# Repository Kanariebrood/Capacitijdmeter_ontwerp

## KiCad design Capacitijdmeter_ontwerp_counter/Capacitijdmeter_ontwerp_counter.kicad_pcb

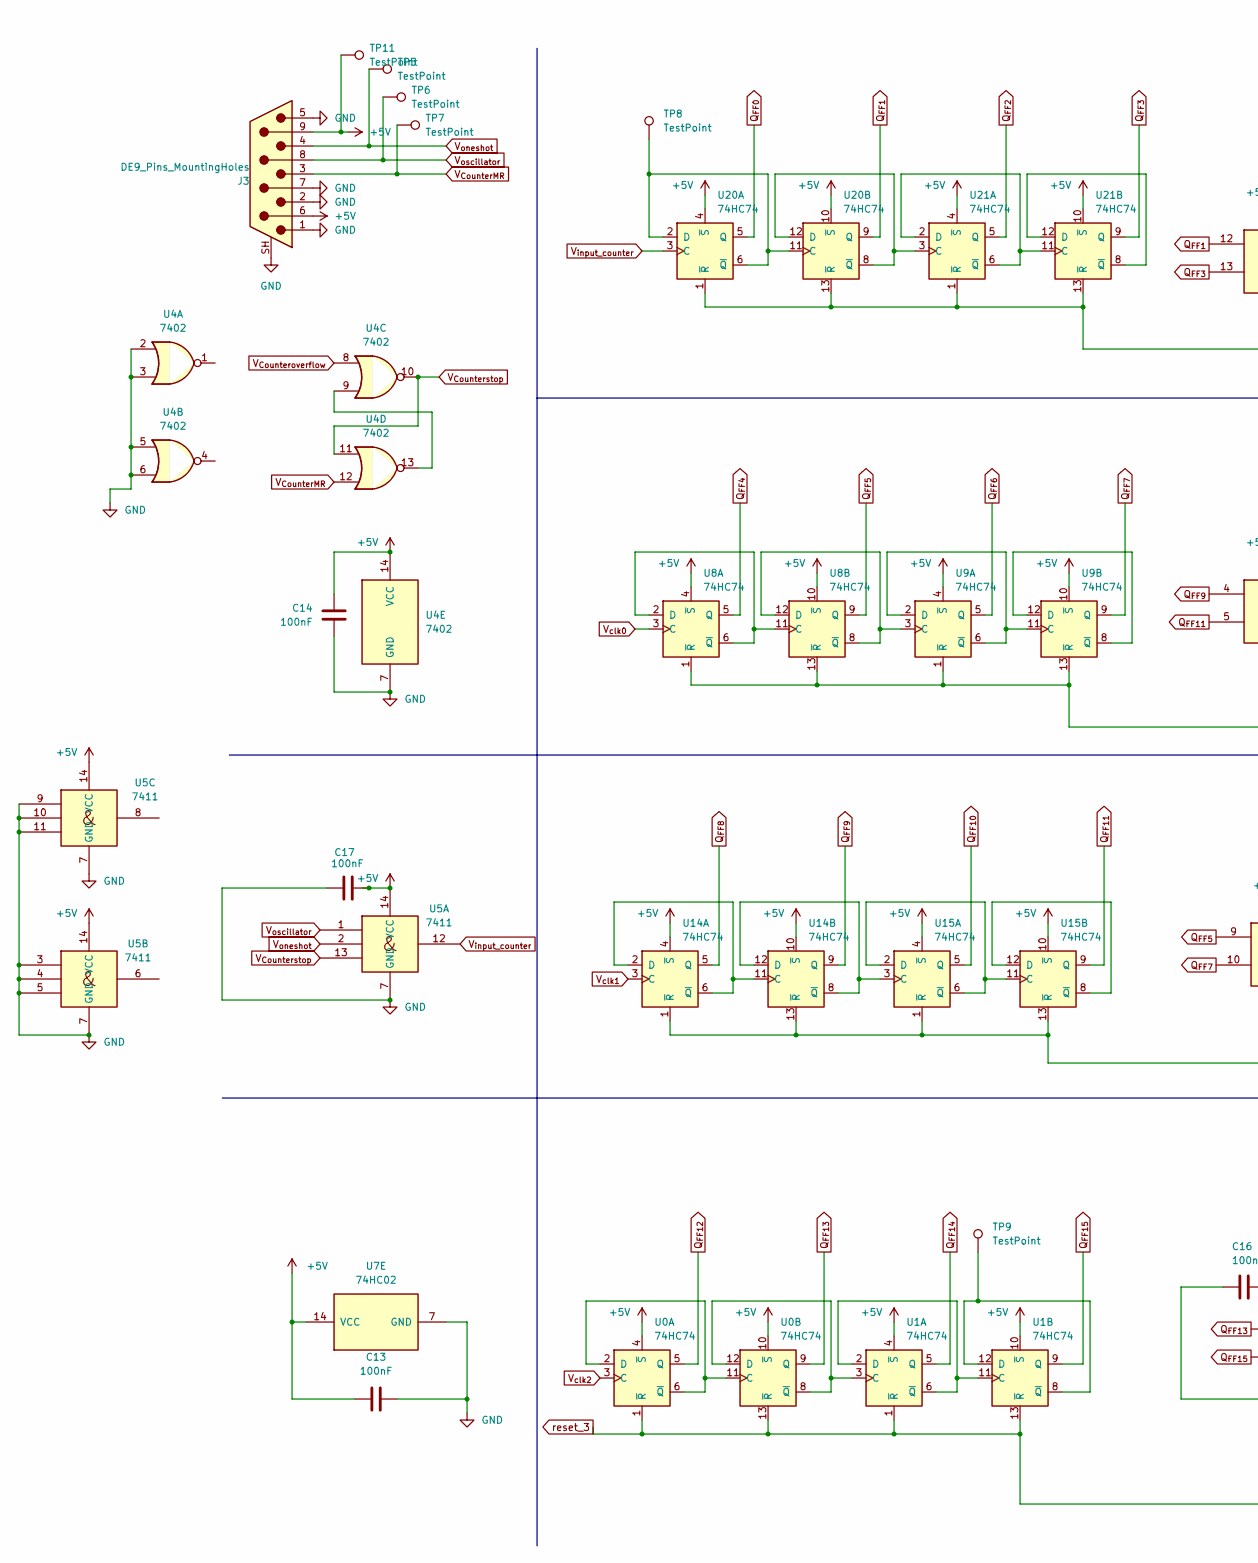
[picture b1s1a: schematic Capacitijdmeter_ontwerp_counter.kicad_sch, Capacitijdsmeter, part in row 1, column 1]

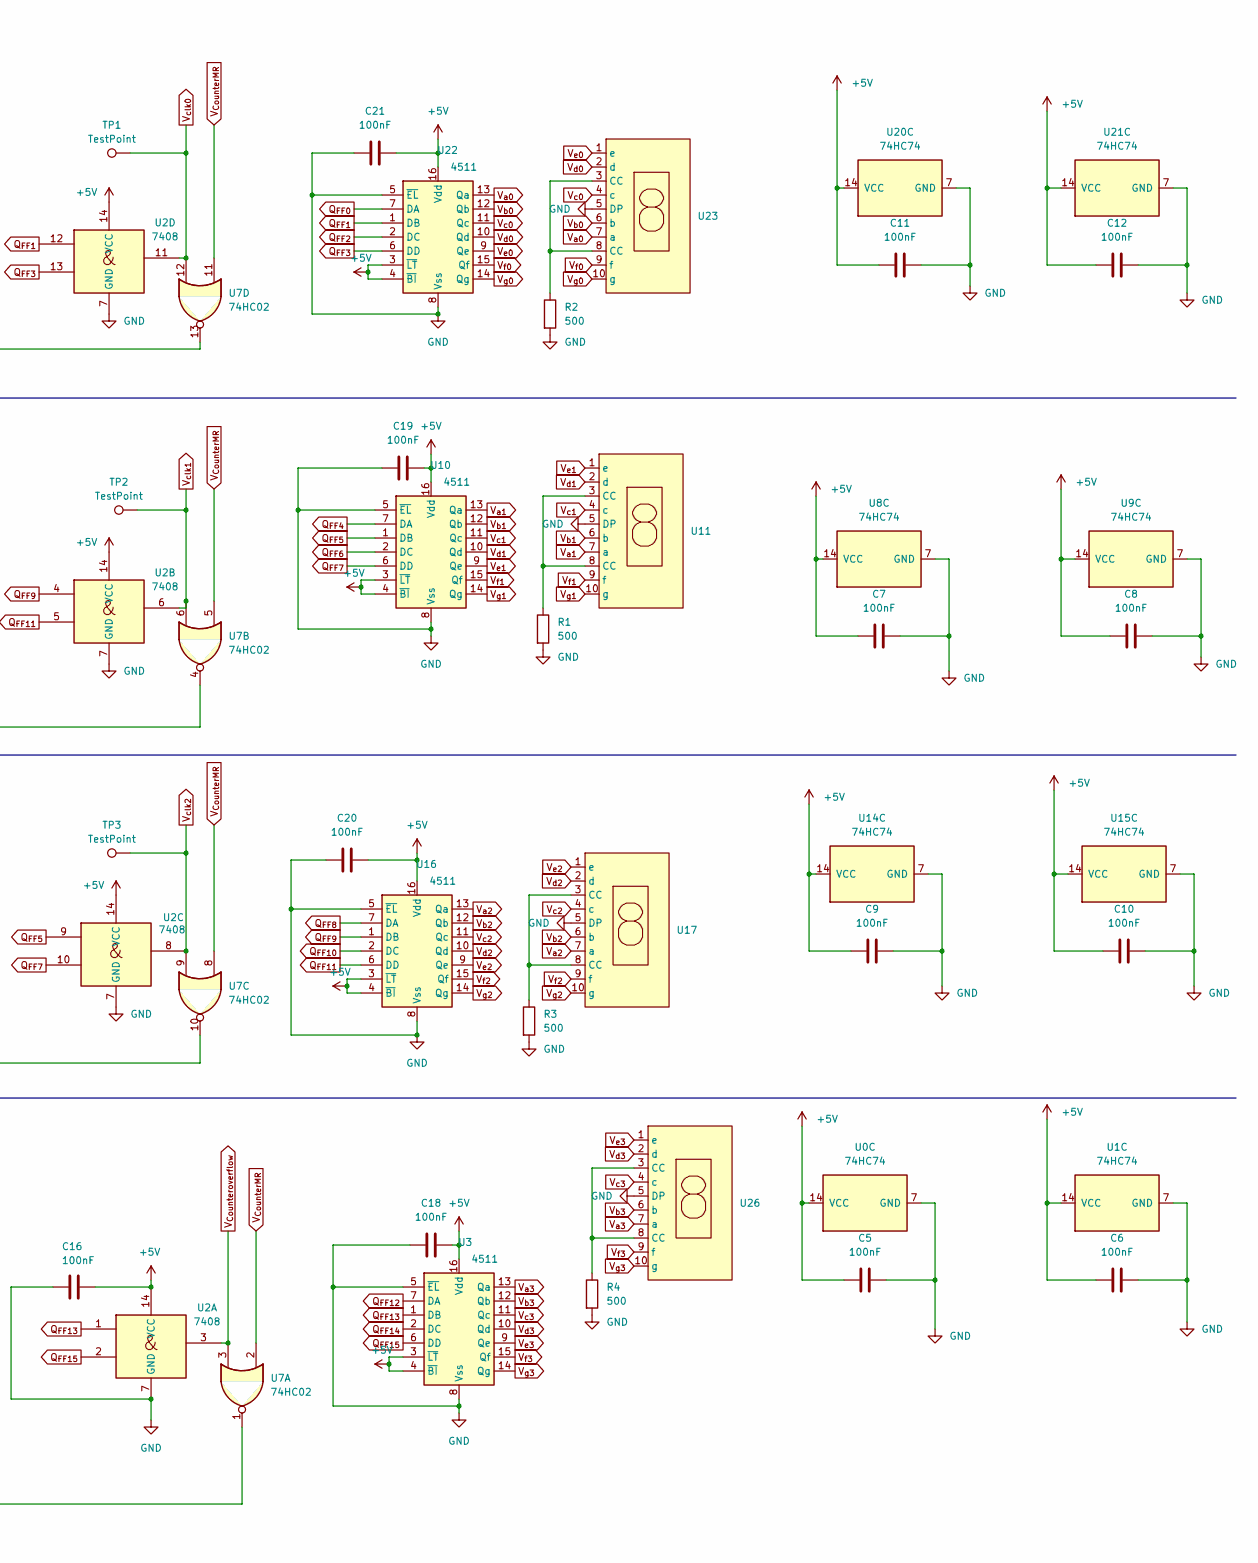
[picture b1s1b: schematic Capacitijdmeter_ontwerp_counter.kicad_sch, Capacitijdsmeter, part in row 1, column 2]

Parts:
C5, C6, C7, C8, C9, C10, C11, C12, C13, C14, C16, C17, C18, C19, C20, C21: 100nF; C_1206_3216Metric_Pad1.33x1.80mm_HandSolder
J3: DE9_Pins_MountingHoles; DSUB-9_Pins_Horizontal_P2.77x2.84mm_EdgePinOffset7.70mm_Hou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
R1, R2, R3, R4: 500; R_1206_3216Metric_Pad1.30x1.75mm_HandSolder
TP1, TP2, TP3, TP5, TP6, TP7, TP8, TP9, TP11: TestPoint; PinHeader_1x01_P1.00mm_Vertical
U0, U1, U8, U9, U14, U15, U20, U21: 74HC74; SOIC-14_3.9x8.7mm_P1.27mm
U2: 7408; SOIC-14_3.9x8.7mm_P1.27mm
U3, U10, U16, U22: 4511; JEITA_SOIC-16_3.9x9.9mm_P1.27mm
U4: 7402; SOIC-14_3.9x8.7mm_P1.27mm
U5: 7411; SOIC-14_3.9x8.7mm_P1.27mm
U7: 74HC02; SOIC-14_3.9x8.7mm_P1.27mm
U11, U17, U23, U26: SC56-11EWA_KNB

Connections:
+5V: C5.1, C6.1, C7.1, C8.1, C9.1, C10.1, C11.1, C12.1, C13.1, C14.2, C16.2, C17.2, C18.1, C19.1, C20.1, C21.1, J3.6, J3.9, TP11.1 (1_1), U0.4 (~S), U0.10 (~S), U0.14 (VCC), U1.4 (~S), U1.10 (~S), U1.14 (VCC), U2.14 (VCC), U3.3 (~LT), U3.4 (~BI), U3.16 (Vdd), U4.14 (VCC), U5.14 (VCC), U7.14 (VCC), U8.4 (~S), U8.10 (~S), U8.14 (VCC), U9.4 (~S), U9.10 (~S), U9.14 (VCC), U10.3 (~LT), U10.4 (~BI), U10.16 (Vdd), U14.4 (~S), U14.10 (~S), U14.14 (VCC), U15.4 (~S), U15.10 (~S), U15.14 (VCC), U16.3 (~LT), U16.4 (~BI), U16.16 (Vdd), U20.4 (~S), U20.10 (~S), U20.14 (VCC), U21.4 (~S), U21.10 (~S), U21.14 (VCC), U22.3 (~LT), U22.4 (~BI), U22.16 (Vdd)
GND: C5.2, C6.2, C7.2, C8.2, C9.2, C10.2, C11.2, C12.2, C13.2, C14.1, C16.1, C17.1, C18.2, C19.2, C20.2, C21.2, J3.1, J3.2, J3.5, J3.7, J3.SH (PAD), R1.2, R2.2, R3.2, R4.2, U0.7 (GND), U1.7 (GND), U2.7 (GND), U3.5 (~EL), U3.8 (Vss), U4.2, U4.3, U4.5, U4.6, U4.7 (GND), U5.3, U5.4, U5.5, U5.7 (GND), U5.9, U5.10, U5.11, U7.7 (GND), U8.7 (GND), U9.7 (GND), U10.5 (~EL), U10.8 (Vss), U11.5 (DP), U14.7 (GND), U15.7 (GND), U16.5 (~EL), U16.8 (Vss), U17.5 (DP), U20.7 (GND), U21.7 (GND), U22.5 (~EL), U22.8 (Vss), U23.5 (DP), U26.5 (DP)
unnamed: R1.1, U11.3 (CC), U11.8 (CC)
unnamed: R2.1, U23.3 (CC), U23.8 (CC)
unnamed: R3.1, U17.3 (CC), U17.8 (CC)
unnamed: R4.1, U26.3 (CC), U26.8 (CC)
unnamed: U0.2 (D), U0.6 (~Q), U0.11 (C)
unnamed: U0.8 (~Q), U0.12 (D), U1.3 (C)
unnamed: U1.2 (D), U1.6 (~Q), U1.11 (C)
unnamed: TP9.1 (1_1), U1.8 (~Q), U1.12 (D)
unnamed: U4.9, U4.13
unnamed: U8.2 (D), U8.6 (~Q), U8.11 (C)
unnamed: U7.4, U8.1 (~R), U8.13 (~R), U9.1 (~R), U9.13 (~R)
unnamed: U8.8 (~Q), U8.12 (D), U9.3 (C)
unnamed: U9.2 (D), U9.6 (~Q), U9.11 (C)
unnamed: U9.8 (~Q), U9.12 (D)
unnamed: U14.2 (D), U14.6 (~Q), U14.11 (C)
unnamed: U7.10, U14.1 (~R), U14.13 (~R), U15.1 (~R), U15.13 (~R)
unnamed: U14.8 (~Q), U14.12 (D), U15.3 (C)
unnamed: U15.2 (D), U15.6 (~Q), U15.11 (C)
unnamed: U15.8 (~Q), U15.12 (D)
unnamed: TP8.1 (1_1), U20.2 (D), U20.6 (~Q), U20.11 (C)
unnamed: U7.13, U20.1 (~R), U20.13 (~R), U21.1 (~R), U21.13 (~R)
unnamed: U20.8 (~Q), U20.12 (D), U21.3 (C)
unnamed: U21.2 (D), U21.6 (~Q), U21.11 (C)
unnamed: U21.8 (~Q), U21.12 (D)
Q_{FF0}: U20.5 (Q), U22.7 (DA)
Q_{FF1}: U2.12, U20.9 (Q), U22.1 (DB)
Q_{FF2}: U21.5 (Q), U22.2 (DC)
Q_{FF3}: U2.13, U21.9 (Q), U22.6 (DD)
Q_{FF4}: U8.5 (Q), U10.7 (DA)
Q_{FF5}: U2.9, U8.9 (Q), U10.1 (DB)
Q_{FF6}: U9.5 (Q), U10.2 (DC)
Q_{FF7}: U2.10, U9.9 (Q), U10.6 (DD)
Q_{FF8}: U14.5 (Q), U16.7 (DA)
Q_{FF9}: U2.4, U14.9 (Q), U16.1 (DB)
Q_{FF10}: U15.5 (Q), U16.2 (DC)
Q_{FF11}: U2.5, U15.9 (Q), U16.6 (DD)
Q_{FF12}: U0.5 (Q), U3.7 (DA)
Q_{FF13}: U0.9 (Q), U2.1, U3.1 (DB)
Q_{FF14}: U1.5 (Q), U3.2 (DC)
Q_{FF15}: U1.9 (Q), U2.2, U3.6 (DD)
V_{CounterMR}: J3.3, TP7.1 (1_1), U4.12, U7.2, U7.5, U7.8, U7.11
V_{Counteroverflow}: U2.3, U4.8, U7.3
V_{Counterstop}: U4.10, U4.11, U5.13
V_{a0}: U22.13 (Qa), U23.7 (a)
V_{a1}: U10.13 (Qa), U11.7 (a)
V_{a2}: U16.13 (Qa), U17.7 (a)
V_{a3}: U3.13 (Qa), U26.7 (a)
V_{b0}: U22.12 (Qb), U23.6 (b)
V_{b1}: U10.12 (Qb), U11.6 (b)
V_{b2}: U16.12 (Qb), U17.6 (b)
V_{b3}: U3.12 (Qb), U26.6 (b)
V_{c0}: U22.11 (Qc), U23.4 (c)
V_{c1}: U10.11 (Qc), U11.4 (c)
V_{c2}: U16.11 (Qc), U17.4 (c)
V_{c3}: U3.11 (Qc), U26.4 (c)
V_{clk0}: TP1.1 (1_1), U2.11, U7.12, U8.3 (C)
V_{clk1}: TP2.1 (1_1), U2.6, U7.6, U14.3 (C)
V_{clk2}: TP3.1 (1_1), U0.3 (C), U2.8, U7.9
V_{d0}: U22.10 (Qd), U23.2 (d)
V_{d1}: U10.10 (Qd), U11.2 (d)
V_{d2}: U16.10 (Qd), U17.2 (d)
V_{d3}: U3.10 (Qd), U26.2 (d)
V_{e0}: U22.9 (Qe), U23.1 (e)
V_{e1}: U10.9 (Qe), U11.1 (e)
V_{e2}: U16.9 (Qe), U17.1 (e)
V_{e3}: U3.9 (Qe), U26.1 (e)
V_{f0}: U22.15 (Qf), U23.9 (f)
V_{f1}: U10.15 (Qf), U11.9 (f)
V_{f2}: U16.15 (Qf), U17.9 (f)
V_{f3}: U3.15 (Qf), U26.9 (f)
V_{g0}: U22.14 (Qg), U23.10 (g)
V_{g1}: U10.14 (Qg), U11.10 (g)
V_{g2}: U16.14 (Qg), U17.10 (g)
V_{g3}: U3.14 (Qg), U26.10 (g)
V_{input_counter}: U5.12, U20.3 (C)
V_{oneshot}: J3.4, TP5.1 (1_1), U5.2
V_{oscillator}: J3.8, TP6.1 (1_1), U5.1
reset_3: U0.1 (~R), U0.13 (~R), U1.1 (~R), U1.13 (~R), U7.1

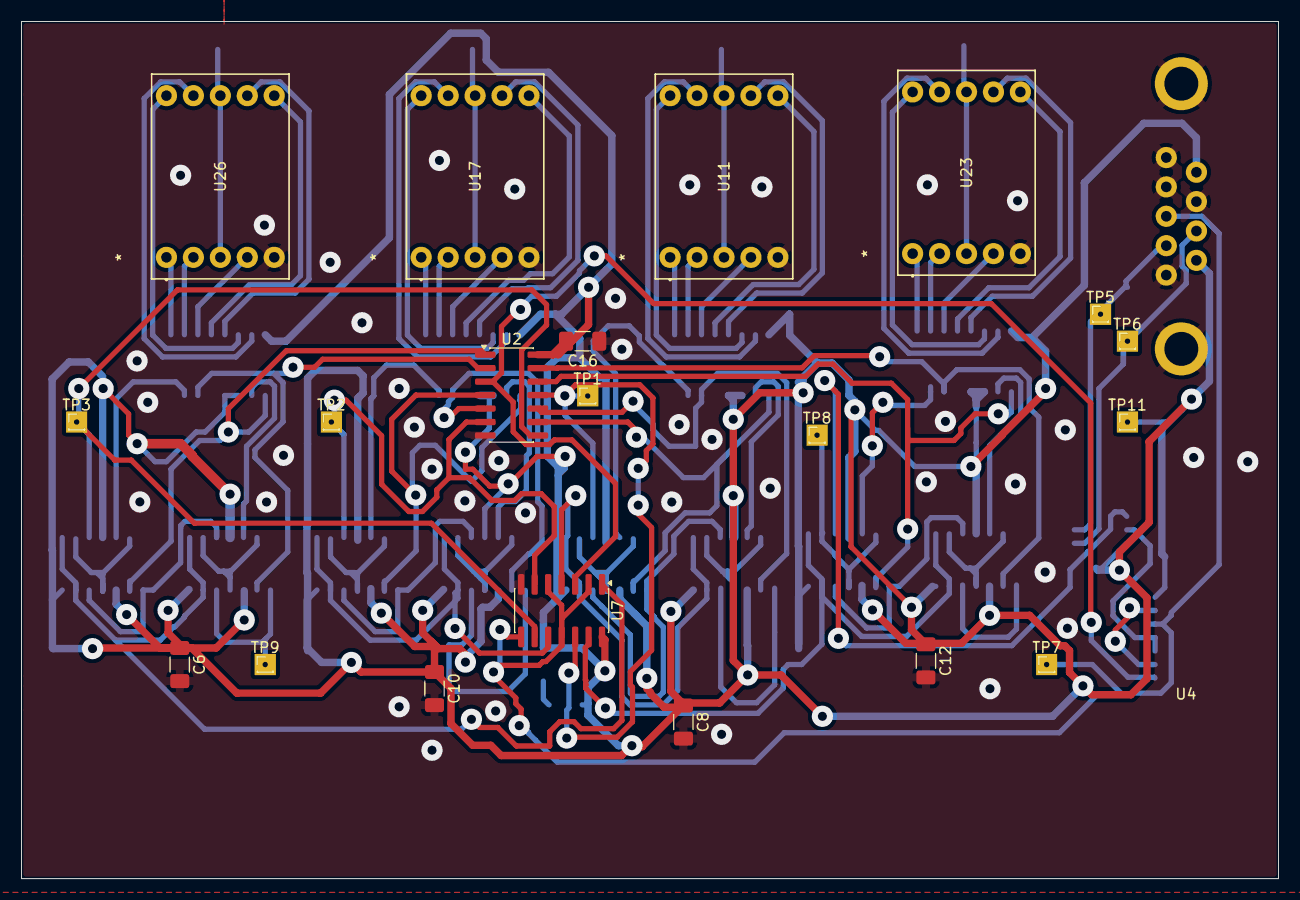
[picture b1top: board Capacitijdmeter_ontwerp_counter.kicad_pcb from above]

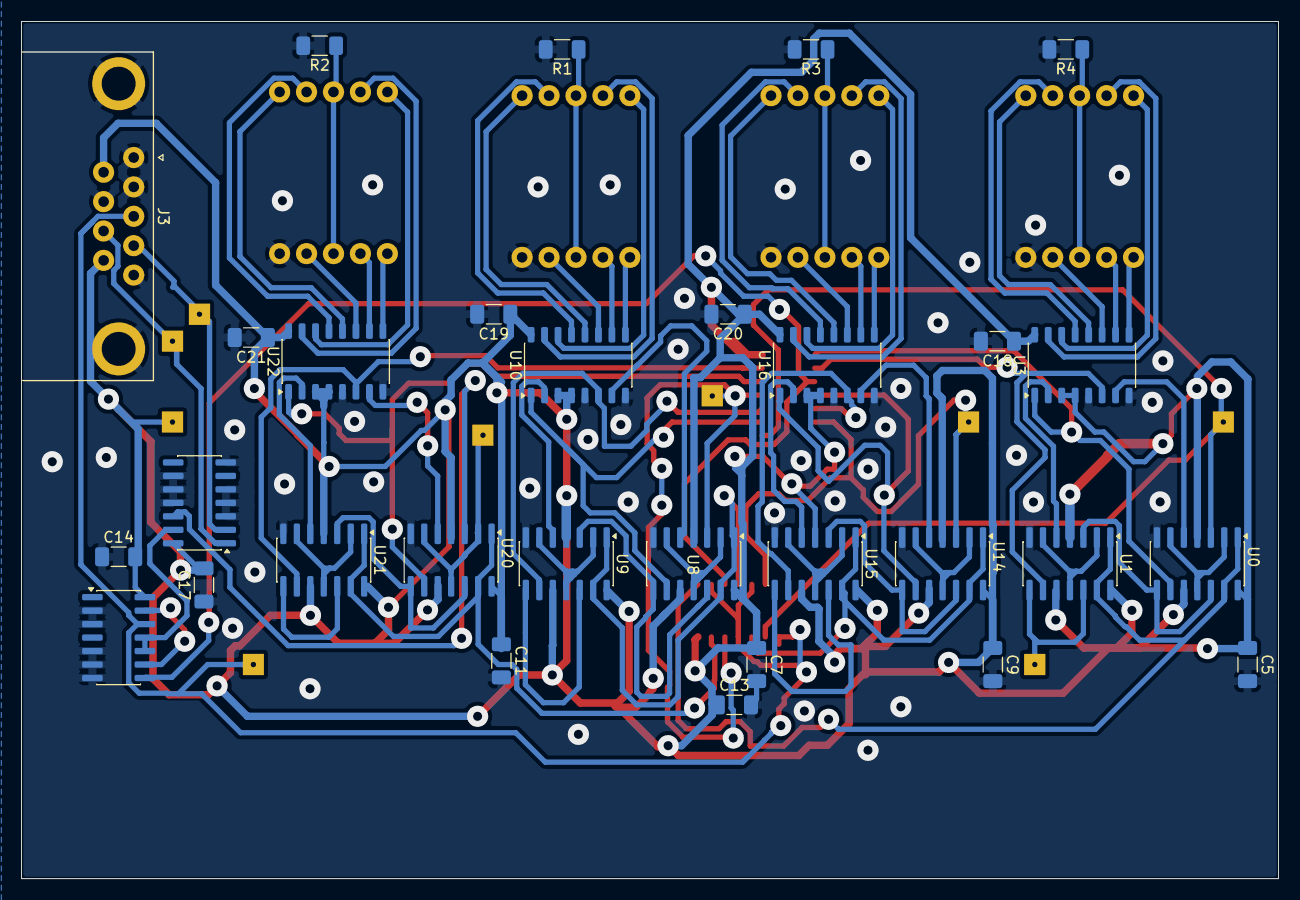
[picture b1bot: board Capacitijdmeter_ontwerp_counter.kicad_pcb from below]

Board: 2 copper layers, 118.5 x 80.8 mm, 50 parts (30 on the bottom side), 80 nets.

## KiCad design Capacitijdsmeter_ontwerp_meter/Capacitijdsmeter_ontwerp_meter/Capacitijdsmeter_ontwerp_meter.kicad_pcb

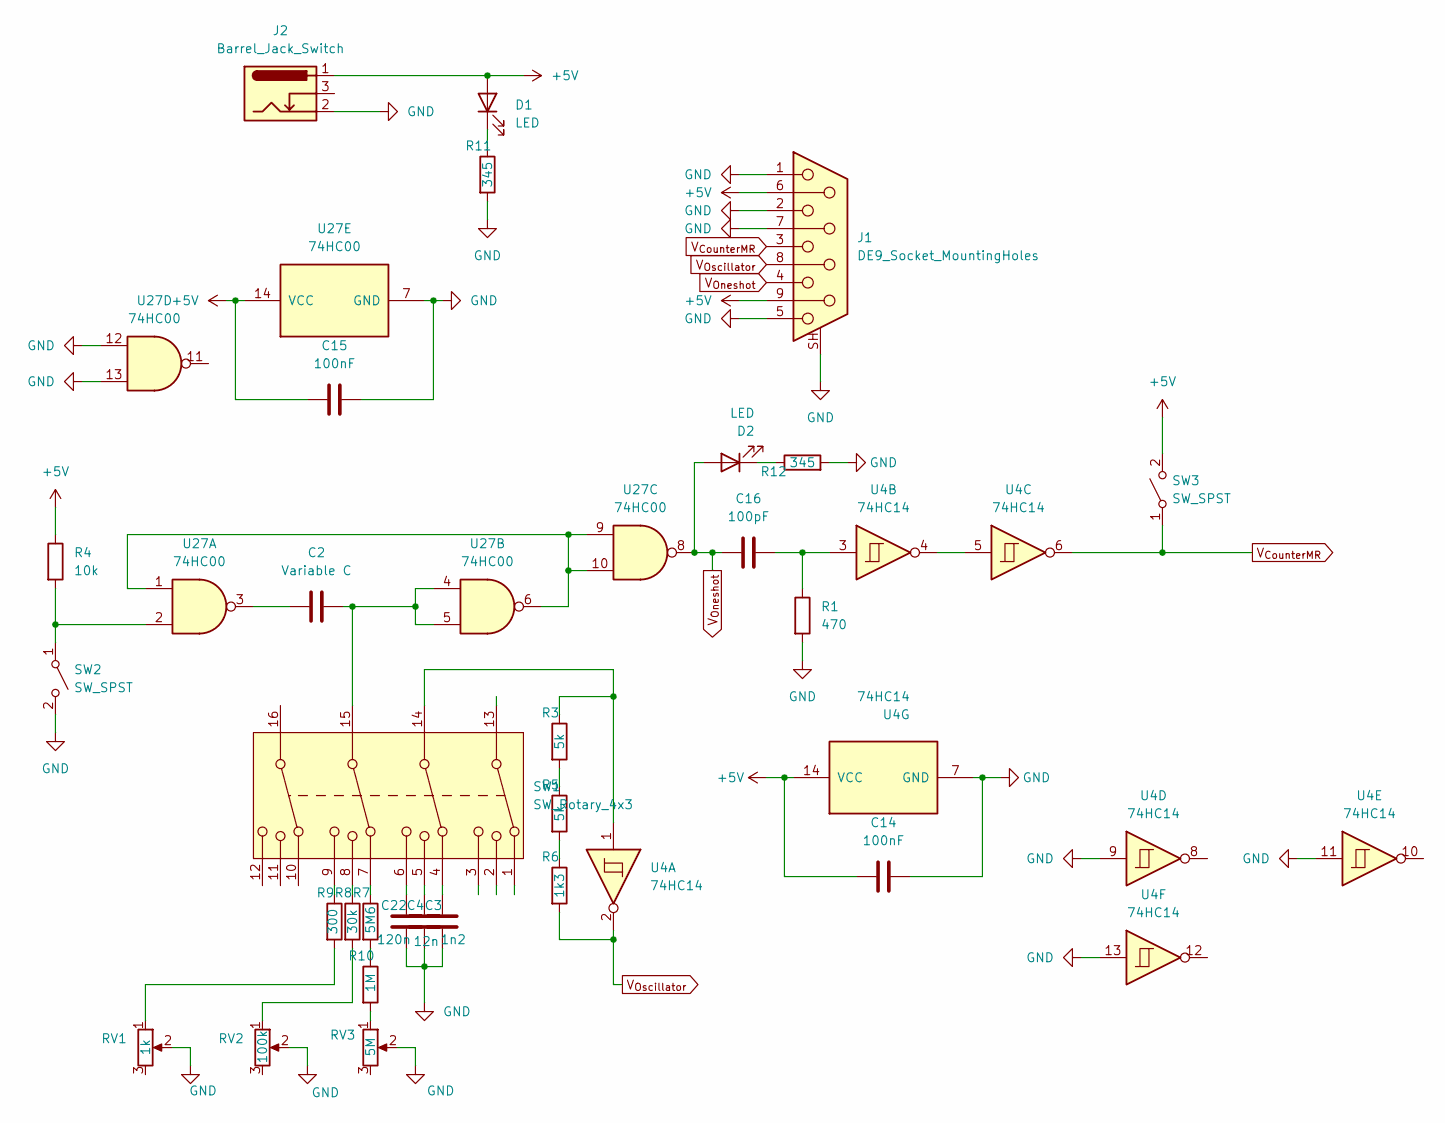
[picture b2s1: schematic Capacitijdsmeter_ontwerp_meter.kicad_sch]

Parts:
C2: Variable C; C_Disc_D5.0mm_W2.5mm_P5.00mm
C3: 1n2; C_Disc_D5.0mm_W2.5mm_P5.00mm
C4: 12n; C_Disc_D5.0mm_W2.5mm_P5.00mm
C14, C15: 100nF; C_Disc_D5.0mm_W2.5mm_P5.00mm
C16: 100pF; C_Disc_D5.0mm_W2.5mm_P5.00mm
C22: 120n; C_Disc_D5.0mm_W2.5mm_P5.00mm
D1, D2: LED; LED_D5.0mm
J1: DE9_Socket_MountingHoles; DSUB-9_Socket_Horizontal_P2.77x2.84mm_EdgePinOffset7.70mm_H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
J2: Barrel_Jack_Switch; BarrelJack_Horizontal
R1: 470; R_Axial_DIN0207_L6.3mm_D2.5mm_P7.62mm_Horizontal
R3, R5: 5k; R_Axial_DIN0207_L6.3mm_D2.5mm_P7.62mm_Horizontal
R4: 10k; R_Axial_DIN0207_L6.3mm_D2.5mm_P7.62mm_Horizontal
R6: 1k3; R_Axial_DIN0207_L6.3mm_D2.5mm_P7.62mm_Horizontal
R7: 5M6; R_Axial_DIN0207_L6.3mm_D2.5mm_P7.62mm_Horizontal
R8: 30k; R_Axial_DIN0207_L6.3mm_D2.5mm_P7.62mm_Horizontal
R9: 300; R_Axial_DIN0207_L6.3mm_D2.5mm_P7.62mm_Horizontal
R10: 1M; R_Axial_DIN0207_L6.3mm_D2.5mm_P7.62mm_Horizontal
R11, R12: 345; R_Axial_DIN0207_L6.3mm_D2.5mm_P7.62mm_Horizontal
RV1: 1k; Potentiometer_Piher_PT-10-V10_Vertical
RV2: 100k; Potentiometer_Piher_PT-10-V10_Vertical
RV3: 5M; Potentiometer_Piher_PT-10-V10_Vertical
SW1: SW_Rotary_4x3; SW_CK1052
SW2: SW_SPST; SW_SPST_Omron_B3F-40xx
SW3: SW_SPST; SW_TH_Tactile_Omron_B3F-100x
U4: 74HC14; DIP-14_W7.62mm_Socket_LongPads
U27: 74HC00; DIP-14_W7.62mm_Socket_LongPads

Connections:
+5V: C14.1, C15.1, D1.2 (A), J1.6, J1.9, J2.1, R4.1, SW3.2 (B), U4.14 (VCC), U27.14 (VCC)
GND: C3.2, C4.2, C14.2, C15.2, C22.2, J1.1, J1.2, J1.5, J1.7, J1.SH (PAD), J2.2, R1.2, R11.2, R12.2, RV1.2, RV2.2, RV3.2, SW2.2 (B), U4.7 (GND), U4.9, U4.11, U4.13, U27.7 (GND), U27.12, U27.13
unnamed: C2.1, U27.3
unnamed: C2.2, SW1.15, U27.4, U27.5
unnamed: C3.1, SW1.4
unnamed: C4.1, SW1.5
unnamed: C16.2, R1.1, U4.3
unnamed: C22.1, SW1.6
unnamed: D1.1 (K), R11.1
unnamed: D2.1 (K), R12.1
unnamed: R3.1, SW1.14, U4.1
unnamed: R3.2, R5.1
unnamed: R5.2, R6.1
unnamed: R7.1, SW1.7
unnamed: R8.1, SW1.8
unnamed: R8.2, RV2.1
unnamed: R9.1, SW1.9
unnamed: R9.2, RV1.1
unnamed: R7.2, R10.1
unnamed: R10.2, RV3.1
unnamed: R4.2, SW2.1 (A), U27.2
unnamed: U4.4, U4.5
unnamed: U27.1, U27.6, U27.9, U27.10
V_{CounterMR}: J1.3, SW3.1 (A), U4.6
V_{Oneshot}: C16.1, D2.2 (A), J1.4, U27.8
V_{Oscillator}: J1.8, R6.2, U4.2

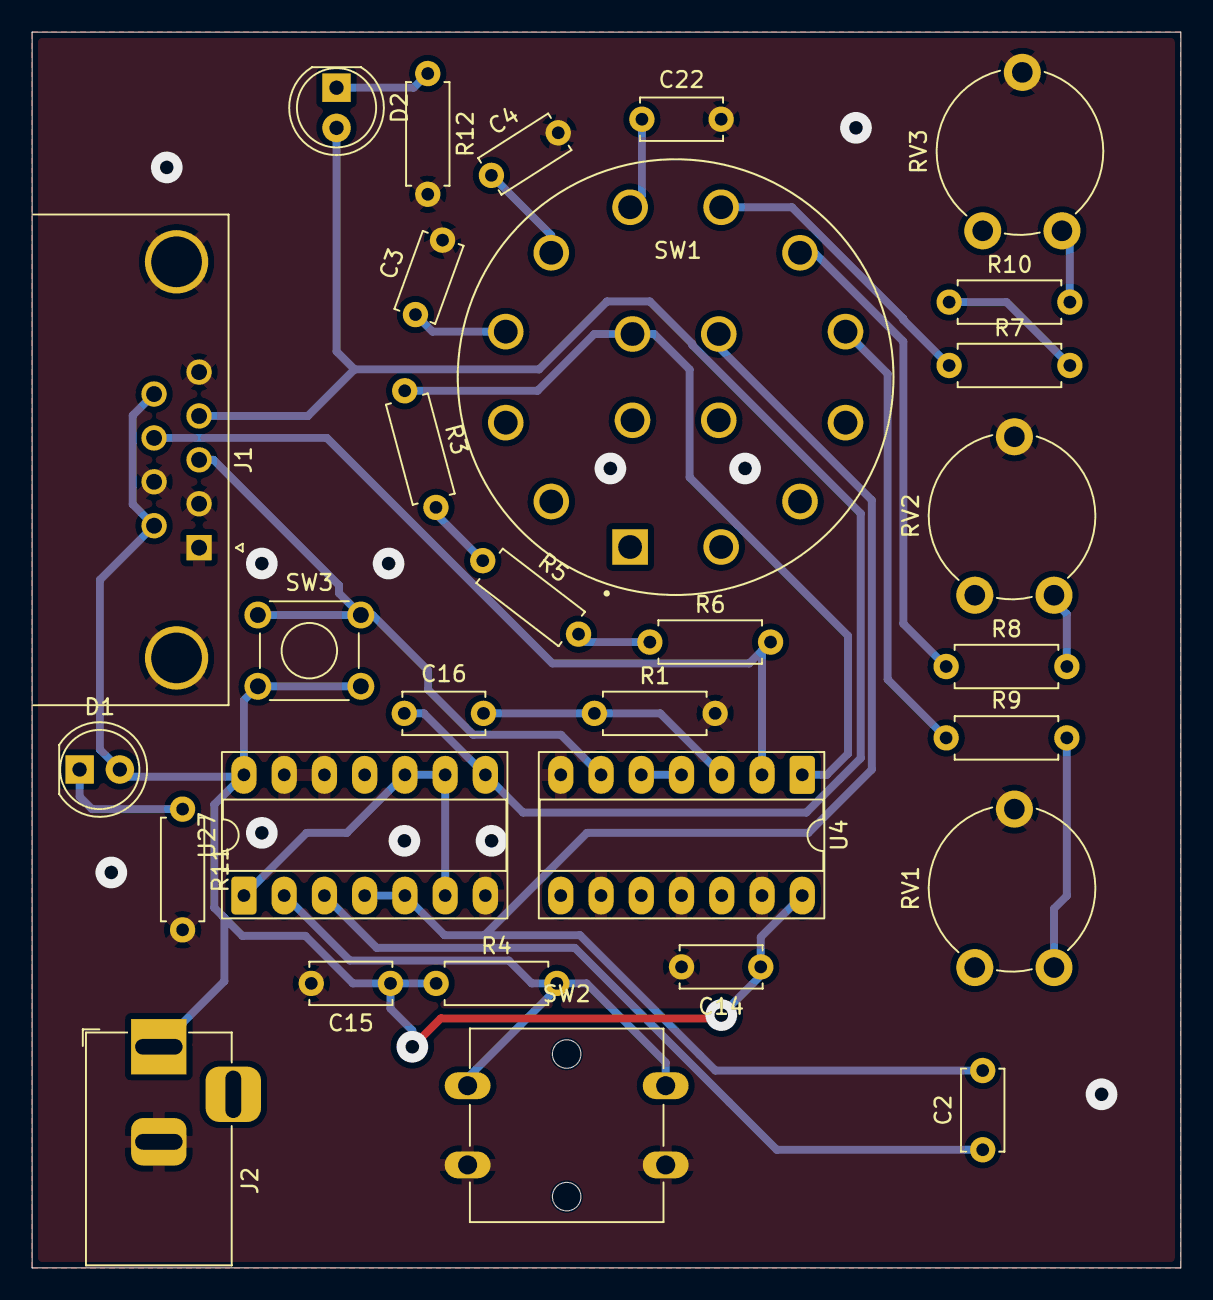
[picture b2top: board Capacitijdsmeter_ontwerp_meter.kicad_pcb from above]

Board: 2 copper layers, 72.5 x 78.0 mm, 30 parts (0 on the bottom side), 26 nets.
